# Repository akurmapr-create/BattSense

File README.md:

# BattSense

**ESP32 Li-ion battery monitor with voltage-based state-of-charge estimation, a custom KiCad PCB, OLED interface, and unit-tested firmware.**

BattSense is an embedded battery-monitoring system for a single-cell Li-ion battery. It measures battery voltage through a resistive analog front end, estimates battery state of charge (SoC), and displays the result locally on an OLED.

The project was developed from circuit design and breadboard validation through modular firmware, automated testing, PCB design, and enclosure development.

## Features

- Single-cell Li-ion battery voltage measurement
- ESP32 ADC acquisition on GPIO34
- Custom resistive analog front end
- ADC sample averaging
- Voltage-based state-of-charge estimation
- OCV-SoC lookup table with piecewise-linear interpolation
- 128×64 I2C OLED interface
- Modular C++ firmware
- Native unit testing with PlatformIO and Unity
- GitHub Actions continuous integration
- Custom 2-layer KiCad PCB
- Removable ESP32 DevKit architecture
- Through-hole design for hand assembly

## System Architecture

```text
          18650 Li-ion Cell
                  |
                  v
        Analog Voltage Divider
          20.1 kΩ / 13.3 kΩ
                  |
                  v
             GPIO34 ADC
                  |
                  v
           BatteryMonitor
                  |
           Battery Voltage
                  |
                  v
      StateOfChargeEstimator
                  |
           Estimated SoC
                  |
                  v
           DisplayManager
                  |
                  v
          128×64 I2C OLED
```

The firmware separates measurement, battery modeling, and presentation into independent modules.

## Hardware

### Analog Front End

The ESP32 measures the battery through a passive resistive divider.

Rev A uses:

```text
R_UPPER = 20.1 kΩ
R_LOWER = 13.3 kΩ
```

At a maximum single-cell Li-ion voltage of 4.2 V:

\[
V_{ADC}
=
4.2
\left(
\frac{13.3}
{20.1+13.3}
\right)
\approx
1.67V
\]

The divider presents a Thevenin resistance of approximately:

\[
R_{TH}
=
20.1k\Omega \parallel 13.3k\Omega
\approx
8.0k\Omega
\]

to the ESP32 ADC.

### Schematic

The KiCad design includes:

- Battery input
- Voltage-divider analog front end
- Removable 30-pin ESP32 DevKit interface
- OLED I2C interface
- Power and ground connections

Additional analog-front-end documentation is available in [`docs/analog_front_end.md`](docs/analog_front_end.md).

## PCB Design

BattSense Rev A includes a custom **60 mm × 50 mm, 2-layer carrier PCB** designed in KiCad.

### PCB Layout

### 3D Render

The PCB includes:

- Two 1×15 female sockets for a removable ESP32 DevKit
- Through-hole analog-front-end components
- OLED interface
- Battery interface
- B.Cu ground plane
- Three M3 enclosure mounting holes
- ESP32 orientation for left-side USB access

The completed layout passes KiCad design-rule checking with:

```text
Unrouted connections: 0
DRC violations:       0
```

Gerber and drill files have also been generated for Rev A fabrication.

## Firmware Architecture

The firmware is separated into dedicated modules:

```text
BatteryMonitor
      |
      | battery voltage
      v
StateOfChargeEstimator
      |
      | estimated SoC
      v
DisplayManager
      |
      v
OLED
```

### BatteryMonitor

Responsible for:

- ESP32 ADC configuration
- ADC acquisition
- Sample averaging
- ADC-voltage conversion
- Voltage-divider compensation
- Battery-voltage reporting

### StateOfChargeEstimator

Converts measured battery voltage into an estimated state of charge.

### DisplayManager

Presents battery voltage and estimated SoC on the OLED.

## State-of-Charge Estimation

BattSense Rev A uses a **voltage-based state-of-charge estimator**.

A Li-ion open-circuit-voltage versus state-of-charge lookup table is stored in firmware. When the measured voltage falls between two table entries, BattSense performs piecewise-linear interpolation.

For neighboring lookup points:

\[
(V_1,SOC_1)
\]

and

\[
(V_2,SOC_2)
\]

the interpolation factor is:

\[
t =
\frac{V-V_1}
{V_2-V_1}
\]

and the estimated state of charge is:

\[
SOC =
SOC_1 +
t(SOC_2-SOC_1)
\]

Values outside the lookup-table range are clamped to 0% or 100%.

The estimator is independent of ESP32 hardware, allowing it to be tested natively on a development machine.

> **Note:** Voltage-based SoC is an estimate rather than precision fuel gauging. Terminal voltage is affected by cell chemistry, temperature, aging, load current, and relaxation state.

See [`docs/state_of_charge.md`](docs/state_of_charge.md) for additional information about the model and its limitations.

## Testing

The SoC estimator is tested using Unity through PlatformIO's native environment.

Current tests cover:

- Lower-voltage clamping
- Upper-voltage clamping
- Exact lookup-table points
- 100% boundary behavior
- Piecewise-linear interpolation

Current result:

```text
5 test cases
5 succeeded
0 failed
```

Run the tests locally with:

```bash
cd firmware
pio test -e native
```

## Building the Firmware

BattSense uses PlatformIO with the Arduino ESP32 framework.

Clone the repository:

```bash
git clone https://github.com/akurmapr-create/BattSense.git
cd BattSense/firmware
```

Build the ESP32 firmware:

```bash
pio run -e esp32dev
```

Upload to a connected ESP32:

```bash
pio run -e esp32dev --target upload
```

Open the serial monitor:

```bash
pio device monitor
```

## Continuous Integration

BattSense uses GitHub Actions to automatically build and test the firmware on pushes and pull requests.

## Development Process

BattSense has been developed iteratively using physical hardware rather than only simulation.

```text
Requirements
    |
    v
Circuit Design
    |
    v
Breadboard Prototype
    |
    v
Measurement
    |
    v
Failure Identification
    |
    v
Design Revision
    |
    v
Validation
```

The analog front end, ADC acquisition, state-of-charge estimation, OLED interface, and PCB were developed and validated incrementally.

## Repository Structure

```text
BattSense/
|
├── .github/
│   └── workflows/
│       └── firmware.yml
|
├── docs/
│   ├── analog_front_end.md
│   ├── calculations.md
│   └── state_of_charge.md
|
├── firmware/
│   ├── include/
│   ├── src/
│   ├── test/
│   └── platformio.ini
|
├── hardware/
│   └── schematics/
│       └── BattSense_AFE/
|
├── images/
│   ├── battsense_prototype.jpeg
│   ├── battsense_schematic.png
│   ├── battsense_pcb.png
│   └── battsense_pcb_3d.png
|
└── README.md
```

## Rev A Status

- [x] Battery-voltage analog front end
- [x] Breadboard validation
- [x] ESP32 ADC integration
- [x] ADC averaging
- [x] State-of-charge estimator
- [x] SoC unit tests
- [x] OLED integration
- [x] GitHub Actions CI
- [x] KiCad schematic
- [x] Custom 2-layer PCB
- [x] ERC / DRC validation
- [x] Gerber generation
- [ ] Permanent perfboard assembly
- [ ] SolidWorks enclosure
- [ ] Final voltage validation with reference multimeter

## Roadmap

### Rev A

Complete the physical prototype:

- Assemble the permanent perfboard implementation
- Design and 3D-print the SolidWorks enclosure
- Mount the OLED and battery holder
- Complete final electrical validation

### Future Revisions

Potential improvements include:

- Cell-specific OCV-SoC characterization
- Current sensing
- Coulomb counting
- Temperature compensation
- Load-compensated SoC estimation
- Dedicated fuel-gauge evaluation
- Custom integrated ESP32 PCB

## Tools

- ESP32
- C++ / Arduino
- PlatformIO
- Unity
- GitHub Actions
- KiCad
- SolidWorks
- Git / GitHub

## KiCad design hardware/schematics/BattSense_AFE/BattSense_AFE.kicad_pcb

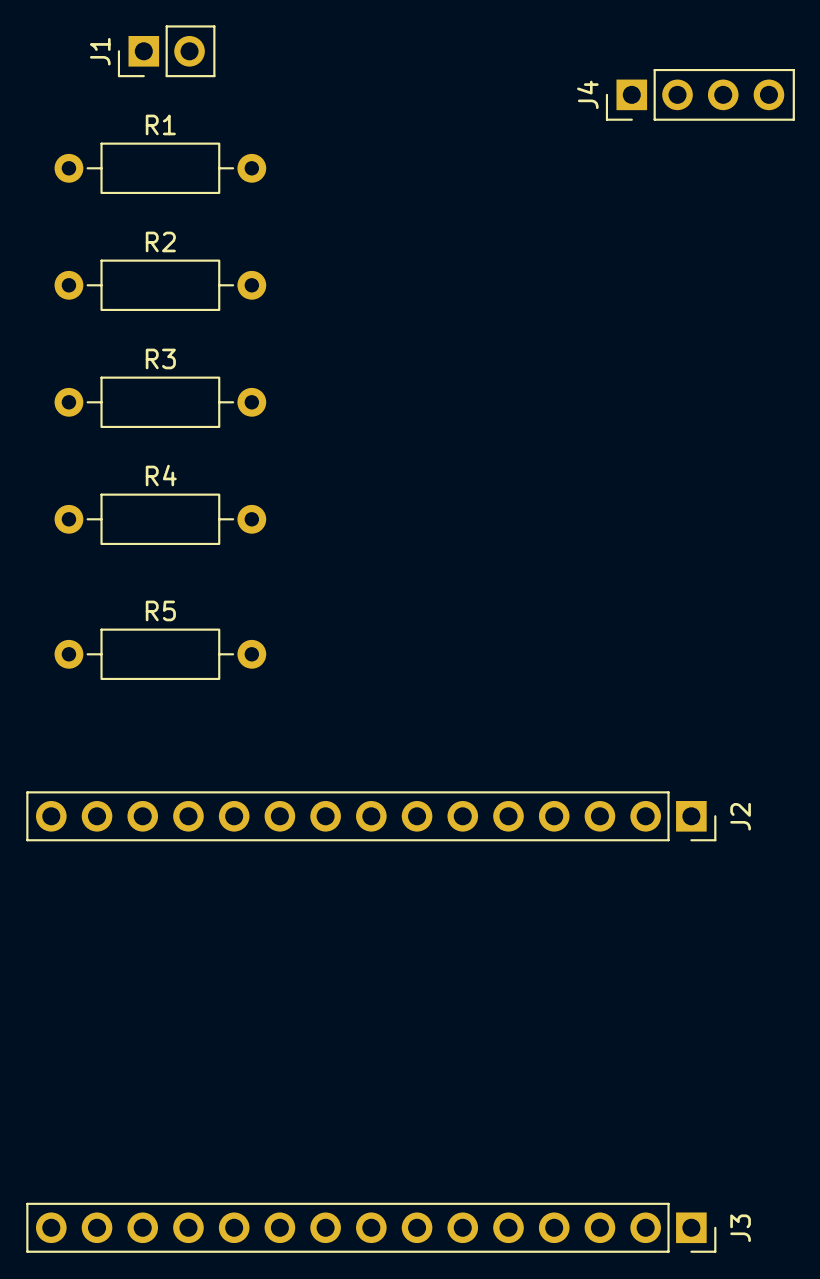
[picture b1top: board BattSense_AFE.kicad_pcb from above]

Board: 2 copper layers, 9 parts (0 on the bottom side), 9 nets, no tracks yet.

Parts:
J1: Battery; PinHeader_1x02_P2.54mm_Vertical
J2: ESP32_LEFT; PinSocket_1x15_P2.54mm_Vertical
J3: ESP32_RIGHT; PinSocket_1x15_P2.54mm_Vertical
J4: OLED; PinHeader_1x04_P2.54mm_Vertical
R1, R4: 10k; R_Axial_DIN0207_L6.3mm_D2.5mm_P10.16mm_Horizontal
R2: 6.8k; R_Axial_DIN0207_L6.3mm_D2.5mm_P10.16mm_Horizontal
R3, R5: 3.3k; R_Axial_DIN0207_L6.3mm_D2.5mm_P10.16mm_Horizontal

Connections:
/+3.3V: J3.15, J4.2
/ADC_SENSE: J2.4, R3.2, R4.1
/OLED_SCL: J3.2, J4.3
/OLED_SDA: J3.5, J4.4
/VBAT: J1.1, R1.1
GND: J1.2, J2.14, J3.14, J4.1, R5.2
unnamed: R1.2, R2.1
unnamed: R2.2, R3.1
unnamed: R4.2, R5.1
